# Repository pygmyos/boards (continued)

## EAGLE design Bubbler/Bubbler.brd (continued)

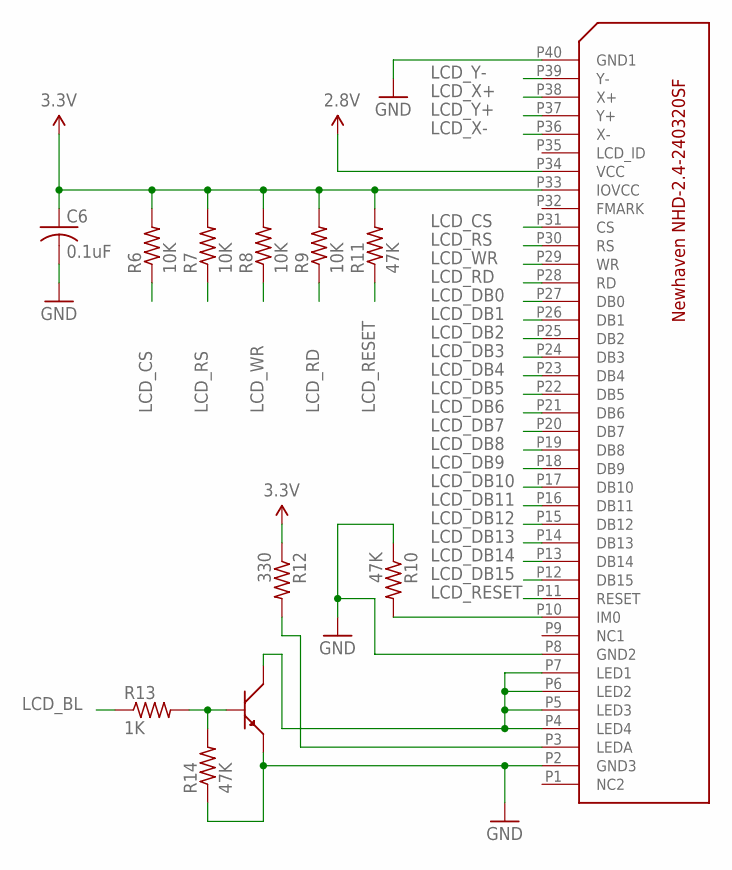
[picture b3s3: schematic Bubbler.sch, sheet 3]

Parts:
C6: 0.1uF; C0402
R6, R7, R8, R9: 10K; R0402
R10, R11, R14: 47K; R0402
R12: 330; R1206
R13: 1K; R0402
U4: BIPOLAR-PMBT6428; DUBLIB_SOT23
U$10: NHD-2.4-240320SF; MOLEX-534132-060

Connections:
2.8V: U$10.P34 (VCC); also elsewhere on the board
3.3V: C6.1, R6.2, R7.2, R8.2, R9.2, R11.2, R12.1, U$10.P33 (IOVCC); also elsewhere on the board
GND: C6.2, R10.1, R14.1, U4.2, U$10.P2 (GND3), U$10.P8 (GND2), U$10.P40 (GND1); also elsewhere on the board
LCD_BL: R13.1; also elsewhere on the board
LCD_CS: R6.1, U$10.P31 (CS); also elsewhere on the board
LCD_DB0: U$10.P27 (DB0); also elsewhere on the board
LCD_DB1: U$10.P26 (DB1); also elsewhere on the board
LCD_DB2: U$10.P25 (DB2); also elsewhere on the board
LCD_DB3: U$10.P24 (DB3); also elsewhere on the board
LCD_DB4: U$10.P23 (DB4); also elsewhere on the board
LCD_DB5: U$10.P22 (DB5); also elsewhere on the board
LCD_DB6: U$10.P21 (DB6); also elsewhere on the board
LCD_DB7: U$10.P20 (DB7); also elsewhere on the board
LCD_DB8: U$10.P19 (DB8); also elsewhere on the board
LCD_DB9: U$10.P18 (DB9); also elsewhere on the board
LCD_DB10: U$10.P17 (DB10); also elsewhere on the board
LCD_DB11: U$10.P16 (DB11); also elsewhere on the board
LCD_DB12: U$10.P15 (DB12); also elsewhere on the board
LCD_DB13: U$10.P14 (DB13); also elsewhere on the board
LCD_DB14: U$10.P13 (DB14); also elsewhere on the board
LCD_DB15: U$10.P12 (DB15); also elsewhere on the board
LCD_RD: R9.1, U$10.P28 (RD); also elsewhere on the board
LCD_RESET: R11.1, U$10.P11 (RESET); also elsewhere on the board
LCD_RS: R7.1, U$10.P30 (RS); also elsewhere on the board
LCD_WR: R8.1, U$10.P29 (WR); also elsewhere on the board
LCD_X+: U$10.P38 (X+); also elsewhere on the board
LCD_X-: U$10.P36 (X-); also elsewhere on the board
LCD_Y+: U$10.P37 (Y+); also elsewhere on the board
LCD_Y-: U$10.P39 (Y-); also elsewhere on the board
unnamed: R10.2, U$10.P10 (IM0)
unnamed: R12.2, U$10.P3 (LEDA)
unnamed: U4.3, U$10.P4 (LED4), U$10.P5 (LED3), U$10.P6 (LED2), U$10.P7 (LED1)
unnamed: R13.2, R14.2, U4.1

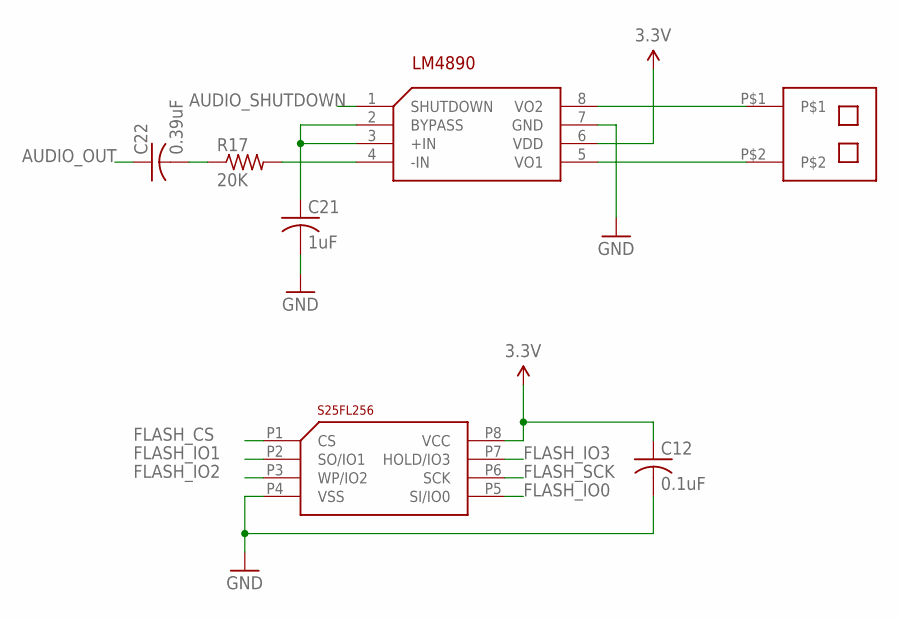
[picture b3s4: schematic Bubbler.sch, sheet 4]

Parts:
C12: 0.1uF; C0402
C21: 1uF; C0402
C22: 0.39uF; C0402
R17: 20K; R0402
U2: SPANSION-S25FL256; SPANSION-WSON-8
U3: LM4890; TSSOP8
U7: MOLEX-1.25-WTB-RA-CONN-2POS; MOLEX-1.25WTB-RA-CONN

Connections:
3.3V: C12.1, U2.P8 (VCC), U3.6 (VDD); also elsewhere on the board
AUDIO_OUT: C22.1; also elsewhere on the board
AUDIO_SHUTDOWN: U3.1 (SHUTDOWN)
FLASH_CS: U2.P1 (CS); also elsewhere on the board
FLASH_IO0: U2.P5 (SI/IO0); also elsewhere on the board
FLASH_IO1: U2.P2 (SO/IO1); also elsewhere on the board
FLASH_IO2: U2.P3 (WP/IO2); also elsewhere on the board
FLASH_IO3: U2.P7 (HOLD/IO3); also elsewhere on the board
FLASH_SCK: U2.P6 (SCK); also elsewhere on the board
GND: C12.2, C21.2, U2.P4 (VSS), U3.7 (GND), U7.P$3 (GND), U7.P$4 (GND); also elsewhere on the board
unnamed: U3.5 (VO1), U7.P$2
unnamed: U3.8 (VO2), U7.P$1
unnamed: C21.1, U3.2 (BYPASS), U3.3 (+IN)
unnamed: R17.2, U3.4 (-IN)
unnamed: C22.2, R17.1

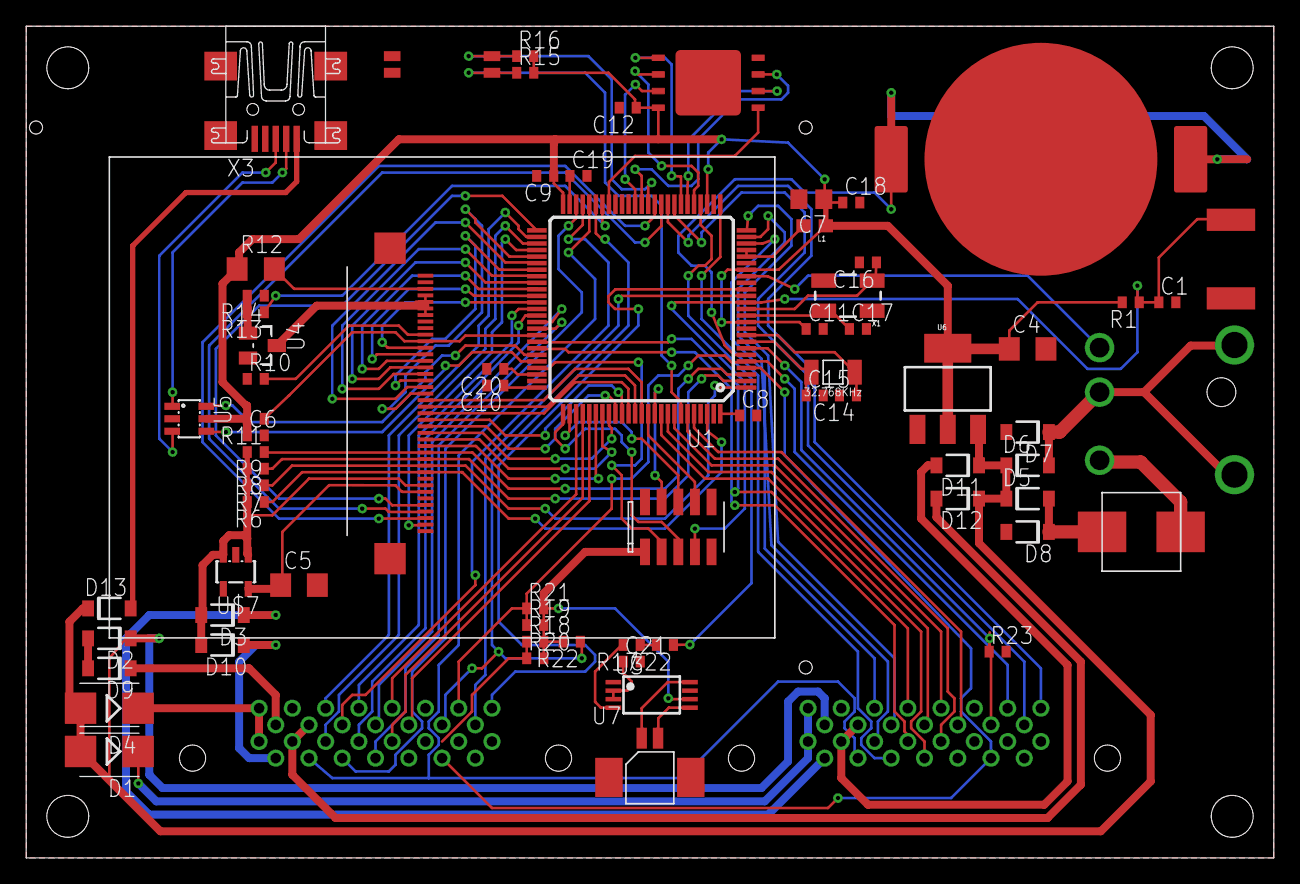
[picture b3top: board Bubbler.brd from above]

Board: 2 copper layers, 95.2 x 63.5 mm, 73 parts (0 on the bottom side), 113 nets.

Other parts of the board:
U$3: NHD-2.4-240320SF-OUTLINE

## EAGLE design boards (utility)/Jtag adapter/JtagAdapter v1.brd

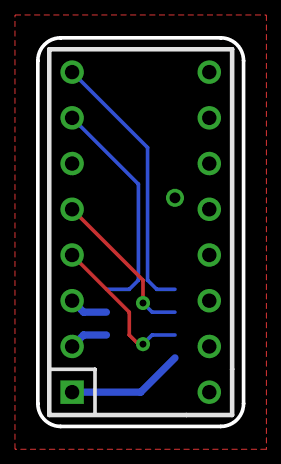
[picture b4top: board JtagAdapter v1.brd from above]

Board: 2 copper layers, 11.4 x 21.6 mm, 3 parts (1 on the bottom side), 8 nets.

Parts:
INFO3: Evan Teitelman; %CC-NC-SA
U$1: STM32-JTAG-10PSTM32-JTAG-ADAPTER(INVERTED); STM32-JTAG-10P
U$2: IDC-DIP-2P16-EIDC-DIP-2P16-E; IDC-DIP-2P16-E

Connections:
3.3V: U$1.2, U$2.P1
GND: U$1.1, U$1.10, U$2.P4, U$2.P6, U$2.P8, U$2.P10, U$2.P12, U$2.P14, U$2.P16
JTCK: U$1.6, U$2.P9
JTDI: U$1.5, U$2.P5
JTDO: U$1.7, U$2.P13
JTMS: U$1.4, U$2.P7
JTRST: U$1.3, U$2.P3
RST: U$1.8, U$2.P15

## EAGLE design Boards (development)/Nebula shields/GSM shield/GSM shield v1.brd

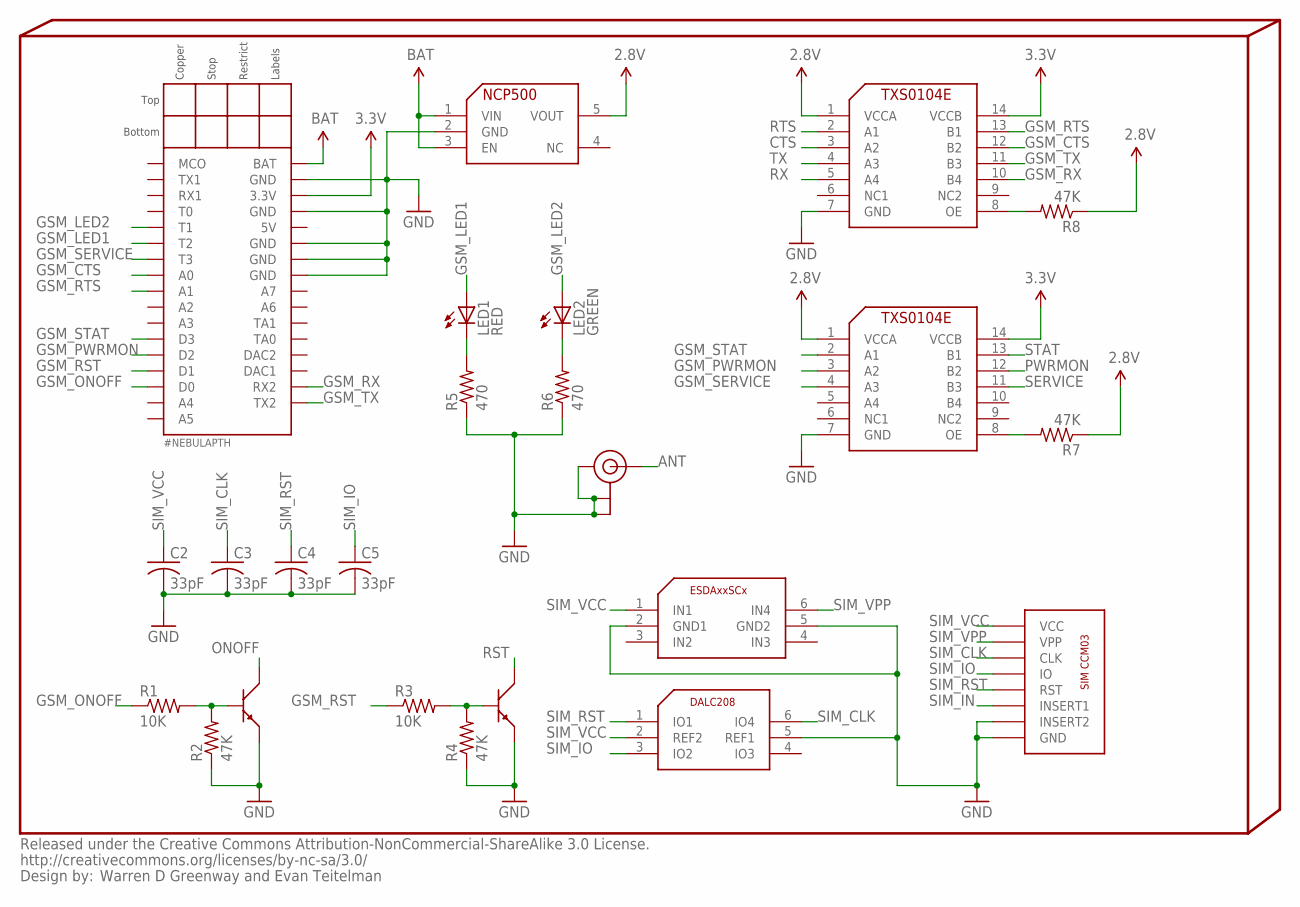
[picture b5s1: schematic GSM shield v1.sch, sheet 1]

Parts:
C2, C3, C4, C5: 33pF; C0402
INFO3: Warren D Greenway and Evan Teitelman; %CC-NC-SA
LED1: RED; LED-0603
LED2: GREEN; LED-0603
NEBULA1: #NEBULAPTH; #NEBULA-PTH
R1, R3: 10K; R0402
R2, R4, R7, R8: 47K; R0402
R5, R6: 470; R0402
U2, U6: BIPOLAR-PMBT6428; DUBLIB_SOT23
U3: NCP500; SOT23-5L
U4: ESDAXXSC6; SOT23-6L
U5: CCM03-3009; CCM03-300X
U7: DALC208; SOT23-6L
U8, U9: INTERFACE-TXS0104E; PW_R-PDSO-G14
U$1: U.FL

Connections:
2.8V: R7.1, R8.1, U3.5 (VOUT), U8.1 (VCCA), U9.1 (VCCA)
3.3V: NEBULA1.3.3V, U8.14 (VCCB), U9.14 (VCCB)
ANT: U$1.P$3 (SIGNAL); also elsewhere on the board
BAT: NEBULA1.BAT, U3.1 (VIN), U3.3 (EN); also elsewhere on the board
CTS: U9.3 (A2); also elsewhere on the board
GND: C2.2, C3.2, C4.2, C5.2, NEBULA1.GND1 (GND), NEBULA1.GND2 (GND), NEBULA1.GND3 (GND), NEBULA1.GND4 (GND), NEBULA1.GND5 (GND), R2.1, R4.1, R5.1, R6.1, U2.2, U3.2 (GND), U4.2 (GND1), U4.5 (GND2), U5.C5 (GND), U5.P2 (INSERT2), U6.2, U7.5 (REF1), U8.7 (GND), U9.7 (GND), U$1.P$1 (GND), U$1.P$2 (GND), U$1.P$4 (SHELL); also elsewhere on the board
GSM_CTS: NEBULA1.A0, U9.12 (B2)
GSM_LED1: LED1.A, NEBULA1.T2
GSM_LED2: LED2.A, NEBULA1.T1
GSM_ONOFF: NEBULA1.D0, R1.1
GSM_PWRMON: NEBULA1.D2, U8.3 (A2)
GSM_RST: NEBULA1.D1, R3.1
GSM_RTS: NEBULA1.A1, U9.13 (B1)
GSM_RX: NEBULA1.COM2_RX (RX2), U9.10 (B4)
GSM_SERVICE: NEBULA1.T3, U8.4 (A3)
GSM_STAT: NEBULA1.D3, U8.2 (A1)
GSM_TX: NEBULA1.COM2_TX (TX2), U9.11 (B3)
unnamed: R7.2, U8.8 (OE)
unnamed: R8.2, U9.8 (OE)
unnamed: R1.2, R2.2, U2.1
unnamed: R3.2, R4.2, U6.1
unnamed: LED1.C, R5.2
unnamed: LED2.C, R6.2
ONOFF: U2.3; also elsewhere on the board
PWRMON: U8.12 (B2); also elsewhere on the board
RST: U6.3; also elsewhere on the board
RTS: U9.2 (A1); also elsewhere on the board
RX: U9.5 (A4); also elsewhere on the board
SERVICE: U8.11 (B3); also elsewhere on the board
SIM_CLK: C3.1, U5.C3 (CLK), U7.6 (IO4); also elsewhere on the board
SIM_IN: U5.P1 (INSERT1); also elsewhere on the board
SIM_IO: C5.1, U5.C7 (IO), U7.3 (IO2); also elsewhere on the board
SIM_RST: C4.1, U5.C2 (RST), U7.1 (IO1); also elsewhere on the board
SIM_VCC: C2.1, U4.1 (IN1), U5.C1 (VCC), U7.2 (REF2); also elsewhere on the board
SIM_VPP: U4.6 (IN4), U5.C6 (VPP)
STAT: U8.13 (B1); also elsewhere on the board
TX: U9.4 (A3); also elsewhere on the board

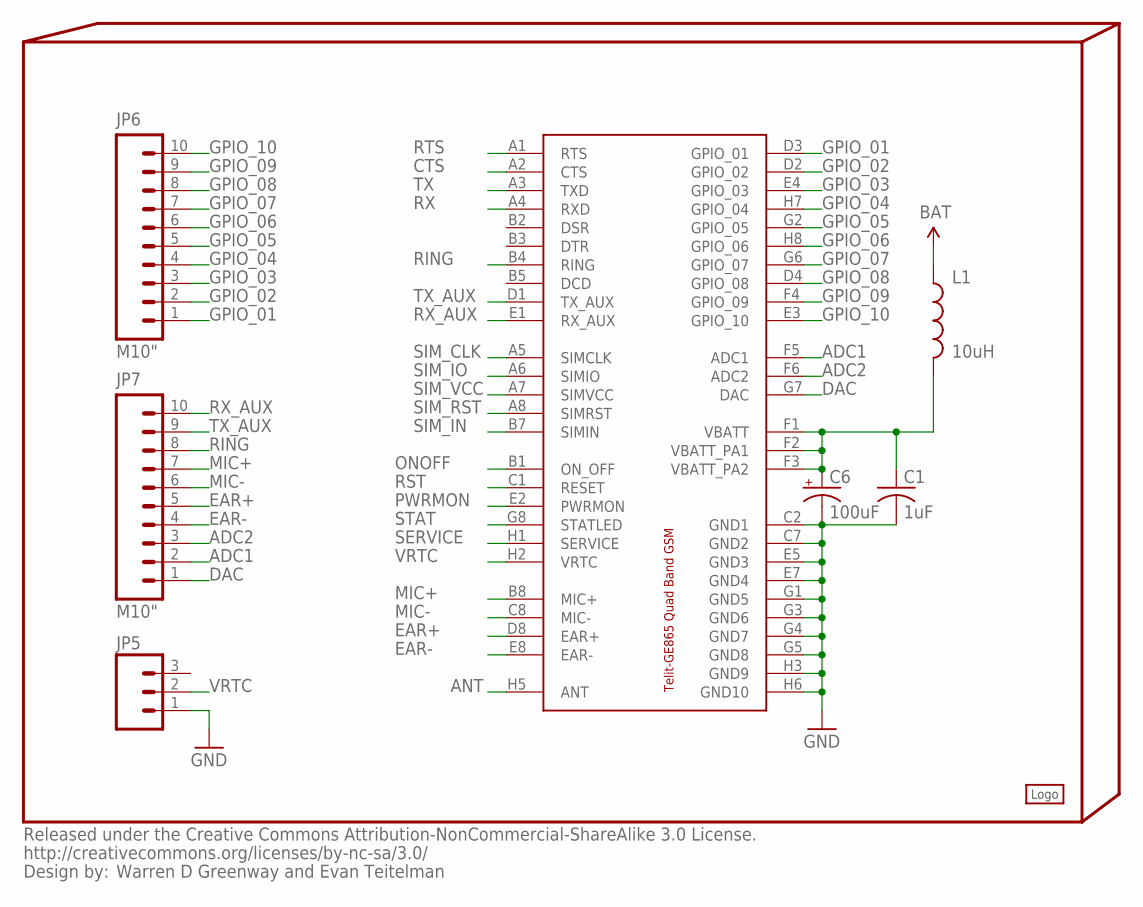
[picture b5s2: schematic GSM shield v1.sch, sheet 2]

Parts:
C1: 1uF; C0402
C6: 100uF; EIA6032
JP5: M03PTH; 1X03
JP6, JP7: M10"; 1X10
L1: 10uH; 1210
LOGO2: #PYGMYLOGOLARGE; #PYGMYLOGO
U11: TELIT-GE865T; TELIT-GE865

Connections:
ADC1: JP7.2, U11.F5 (ADC1)
ADC2: JP7.3, U11.F6 (ADC2)
ANT: U11.H5 (ANT); also elsewhere on the board
BAT: L1.1; also elsewhere on the board
CTS: U11.A2 (CTS); also elsewhere on the board
DAC: JP7.1, U11.G7 (DAC)
EAR+: JP7.5, U11.D8 (EAR+)
EAR-: JP7.4, U11.E8 (EAR-)
GND: C1.2, C6.P$2 (-), JP5.1, U11.C2 (GND1), U11.C7 (GND2), U11.E5 (GND3), U11.E7 (GND4), U11.G1 (GND5), U11.G3 (GND6), U11.G4 (GND7), U11.G5 (GND8), U11.H3 (GND9), U11.H6 (GND10); also elsewhere on the board
GPIO_01: JP6.1, U11.D3 (GPIO_01)
GPIO_02: JP6.2, U11.D2 (GPIO_02)
GPIO_03: JP6.3, U11.E4 (GPIO_03)
GPIO_04: JP6.4, U11.H7 (GPIO_04)
GPIO_05: JP6.5, U11.G2 (GPIO_05)
GPIO_06: JP6.6, U11.H8 (GPIO_06)
GPIO_07: JP6.7, U11.G6 (GPIO_07)
GPIO_08: JP6.8, U11.D4 (GPIO_08)
GPIO_09: JP6.9, U11.F4 (GPIO_09)
GPIO_10: JP6.10, U11.E3 (GPIO_10)
MIC+: JP7.7, U11.B8 (MIC+)
MIC-: JP7.6, U11.C8 (MIC-)
unnamed: C1.1, C6.P$1 (+), L1.2, U11.F1 (VBATT), U11.F2 (VBATT_PA1), U11.F3 (VBATT_PA2)
ONOFF: U11.B1 (ON_OFF); also elsewhere on the board
PWRMON: U11.E2 (PWRMON); also elsewhere on the board
RING: JP7.8, U11.B4 (RING)
RST: U11.C1 (RESET); also elsewhere on the board
RTS: U11.A1 (RTS); also elsewhere on the board
RX: U11.A4 (RXD); also elsewhere on the board
RX_AUX: JP7.10, U11.E1 (RX_AUX)
SERVICE: U11.H1 (SERVICE); also elsewhere on the board
SIM_CLK: U11.A5 (SIMCLK); also elsewhere on the board
SIM_IN: U11.B7 (SIMIN); also elsewhere on the board
SIM_IO: U11.A6 (SIMIO); also elsewhere on the board
SIM_RST: U11.A8 (SIMRST); also elsewhere on the board
SIM_VCC: U11.A7 (SIMVCC); also elsewhere on the board
STAT: U11.G8 (STATLED); also elsewhere on the board
TX: U11.A3 (TXD); also elsewhere on the board
TX_AUX: JP7.9, U11.D1 (TX_AUX)
VRTC: JP5.2, U11.H2 (VRTC)

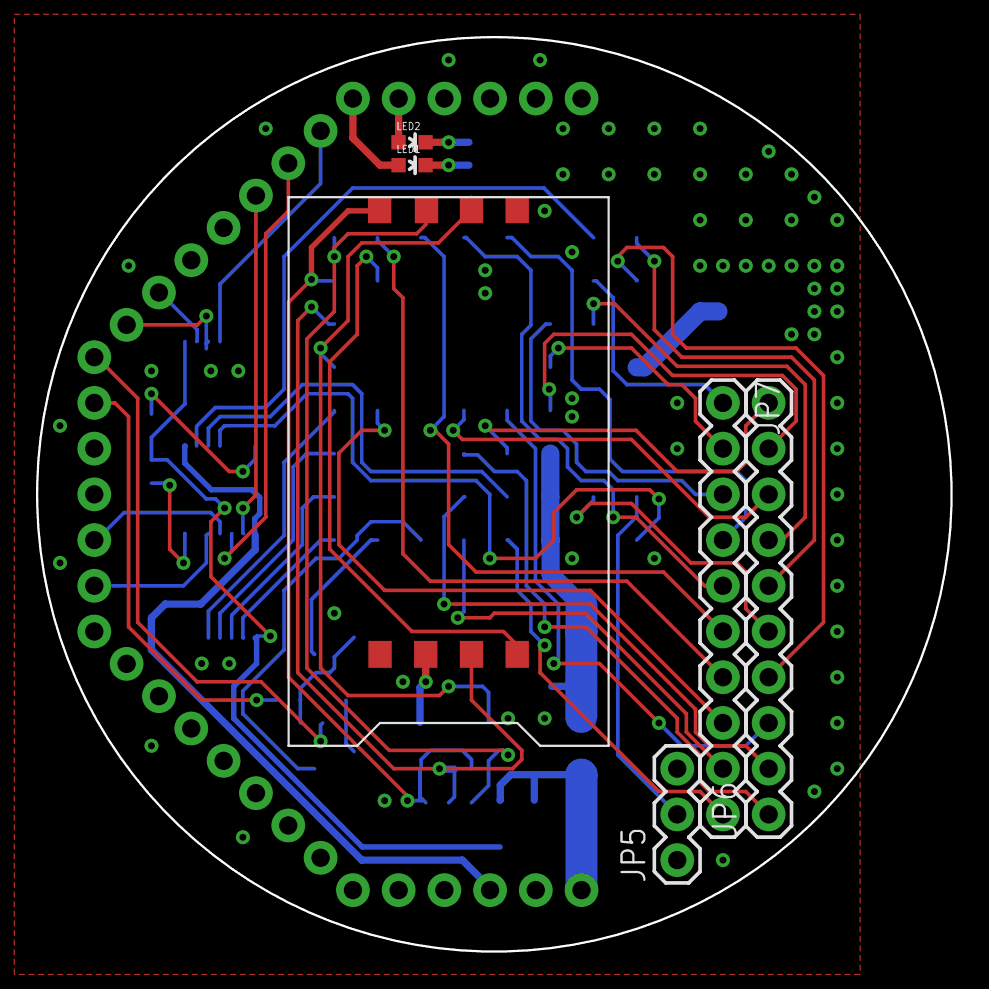
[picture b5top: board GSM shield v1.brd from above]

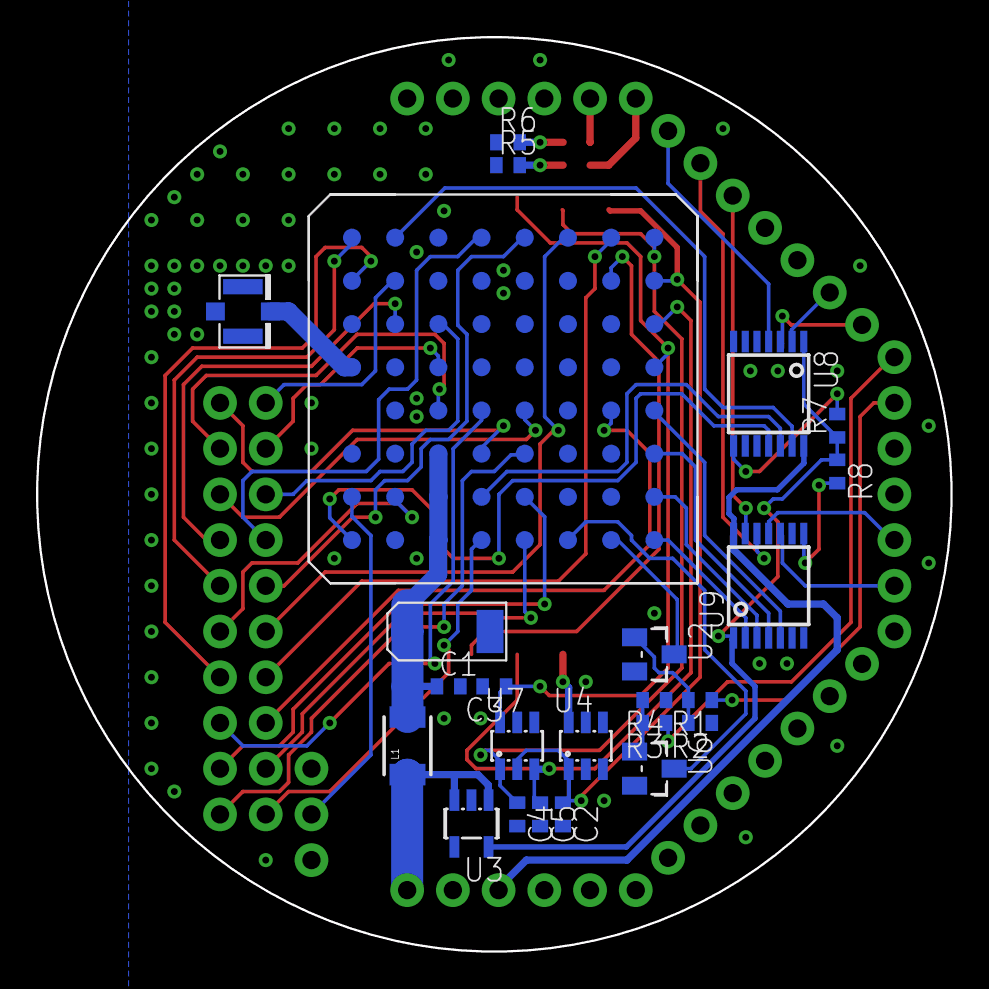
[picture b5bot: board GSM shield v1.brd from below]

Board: 2 copper layers, 50.8 x 50.8 mm, 33 parts (24 on the bottom side), 59 nets.

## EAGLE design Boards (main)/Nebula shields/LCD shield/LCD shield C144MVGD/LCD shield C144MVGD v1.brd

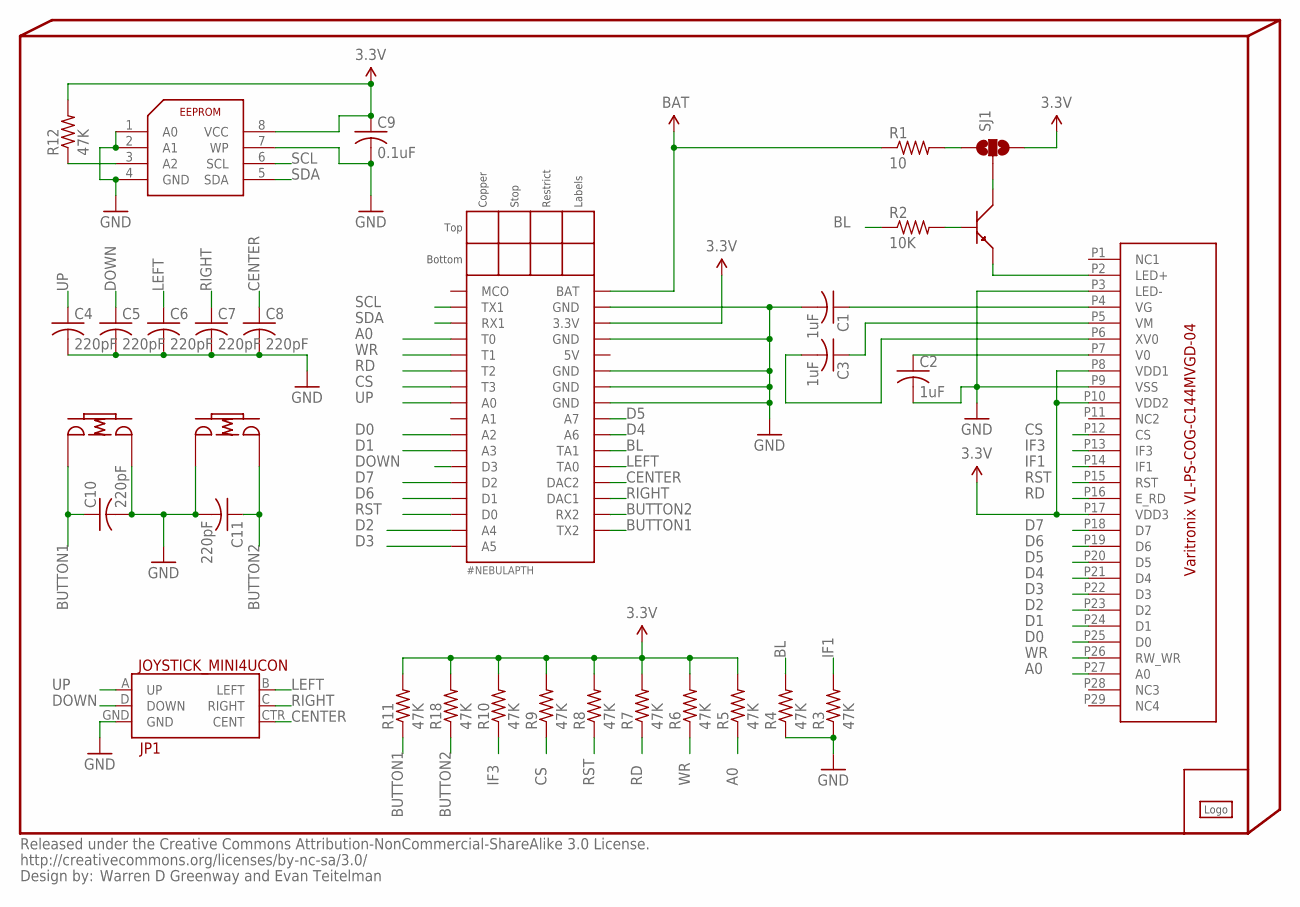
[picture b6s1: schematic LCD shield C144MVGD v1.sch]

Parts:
C1, C2, C3: 1uF; C0402
C4, C5, C6, C7, C8, C10, C11: 220pF; C0402
C9: 0.1uF; C0402
INFO3: Warren D Greenway and Evan Teitelman; %CC-NC-SA
JP1: JOYSTICK_MINI4UCON; JOYSTICK_MINI
LOGO1: #PYGMYLOGOLARGE; #PYGMYLOGO
NEBULA1: #NEBULAPTH; #NEBULA-PTH
R1: 10; R0805
R2: 10K; R0402
R3, R4, R5, R6, R7, R8, R9, R10, R11, R12, R18: 47K; R0402
SJ1: SOLDERJUMPER_2WAYPASTE1&2; SJ_3_PASTE1&2
U1: VARITRONIX_VL-PS-COG-C144MVGD-04FOLDED; VARITRONIX_C144MVGD_FOLDED
U2: BIPOLAR-PMBT6428; DUBLIB_SOT23
U3: EEPROM-ATMEL-AT24HC02B; TSSOP8
U4, U5: SWITCH-ALPS-SKRG; SWITCH-2P-5MM

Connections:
3.3V: C9.1, NEBULA1.3.3V, R5.2, R6.2, R7.2, R8.2, R9.2, R10.2, R11.2, R12.2, R18.2, SJ1.3, U1.P8 (VDD1), U1.P10 (VDD2), U1.P17 (VDD3), U3.8 (VCC)
A0: NEBULA1.T0, R5.1, U1.P27 (A0)
BAT: NEBULA1.BAT, R1.1
BL: NEBULA1.TA1, R2.1, R4.2
BUTTON1: C10.1, NEBULA1.COM2_TX (TX2), R11.1, U4.P1
BUTTON2: C11.1, NEBULA1.COM2_RX (RX2), R18.1, U5.P2
CENTER: C8.1, JP1.CTR (CENT), NEBULA1.DAC2
CS: NEBULA1.T3, R9.1, U1.P12 (CS)
D0: NEBULA1.A2, U1.P25 (D0)
D1: NEBULA1.A3, U1.P24 (D1)
D2: NEBULA1.A4, U1.P23 (D2)
D3: NEBULA1.A5, U1.P22 (D3)
D4: NEBULA1.A6, U1.P21 (D4)
D5: NEBULA1.A7, U1.P20 (D5)
D6: NEBULA1.D1, U1.P19 (D6)
D7: NEBULA1.D2, U1.P18 (D7)
DOWN: C5.1, JP1.D (DOWN), NEBULA1.D3
GND: C1.2, C2.2, C4.2, C5.2, C6.2, C7.2, C8.2, C9.2, C10.2, C11.2, JP1.GND, NEBULA1.GND1 (GND), NEBULA1.GND2 (GND), NEBULA1.GND3 (GND), NEBULA1.GND4 (GND), NEBULA1.GND5 (GND), R3.1, R4.1, U1.P3 (LED-), U1.P9 (VSS), U3.1 (A0), U3.2 (A1), U3.4 (GND), U3.7 (WP), U4.P2, U5.P1
IF1: R3.2, U1.P14 (IF1)
IF3: R10.1, U1.P13 (IF3)
LEFT: C6.1, JP1.B (LEFT), NEBULA1.TA0
unnamed: C1.1, U1.P4 (VG)
unnamed: C3.1, U1.P5 (VM)
unnamed: C3.2, U1.P6 (XV0)
unnamed: C2.1, U1.P7 (V0)
unnamed: SJ1.2, U2.3
unnamed: U1.P2 (LED+), U2.2
unnamed: R2.2, U2.1
unnamed: R1.2, SJ1.1
unnamed: R12.1, U3.3 (A2)
RD: NEBULA1.T2, R7.1, U1.P16 (E_RD)
RIGHT: C7.1, JP1.C (RIGHT), NEBULA1.DAC1
RST: NEBULA1.D0, R8.1, U1.P15 (RST)
SCL: NEBULA1.COM1_TX (TX1), U3.6 (SCL)
SDA: NEBULA1.COM1_RX (RX1), U3.5 (SDA)
UP: C4.1, JP1.A (UP), NEBULA1.A0
WR: NEBULA1.T1, R6.1, U1.P26 (RW_WR)

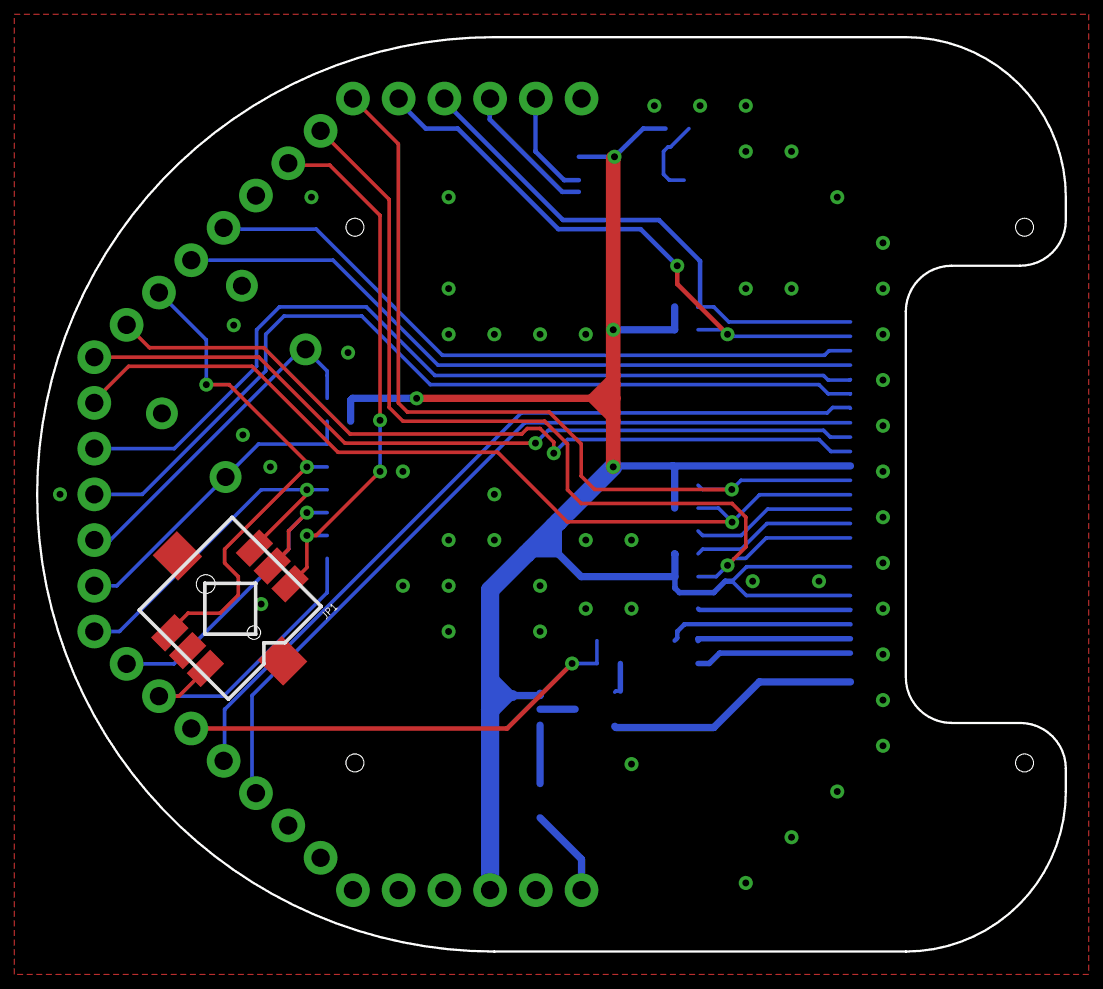
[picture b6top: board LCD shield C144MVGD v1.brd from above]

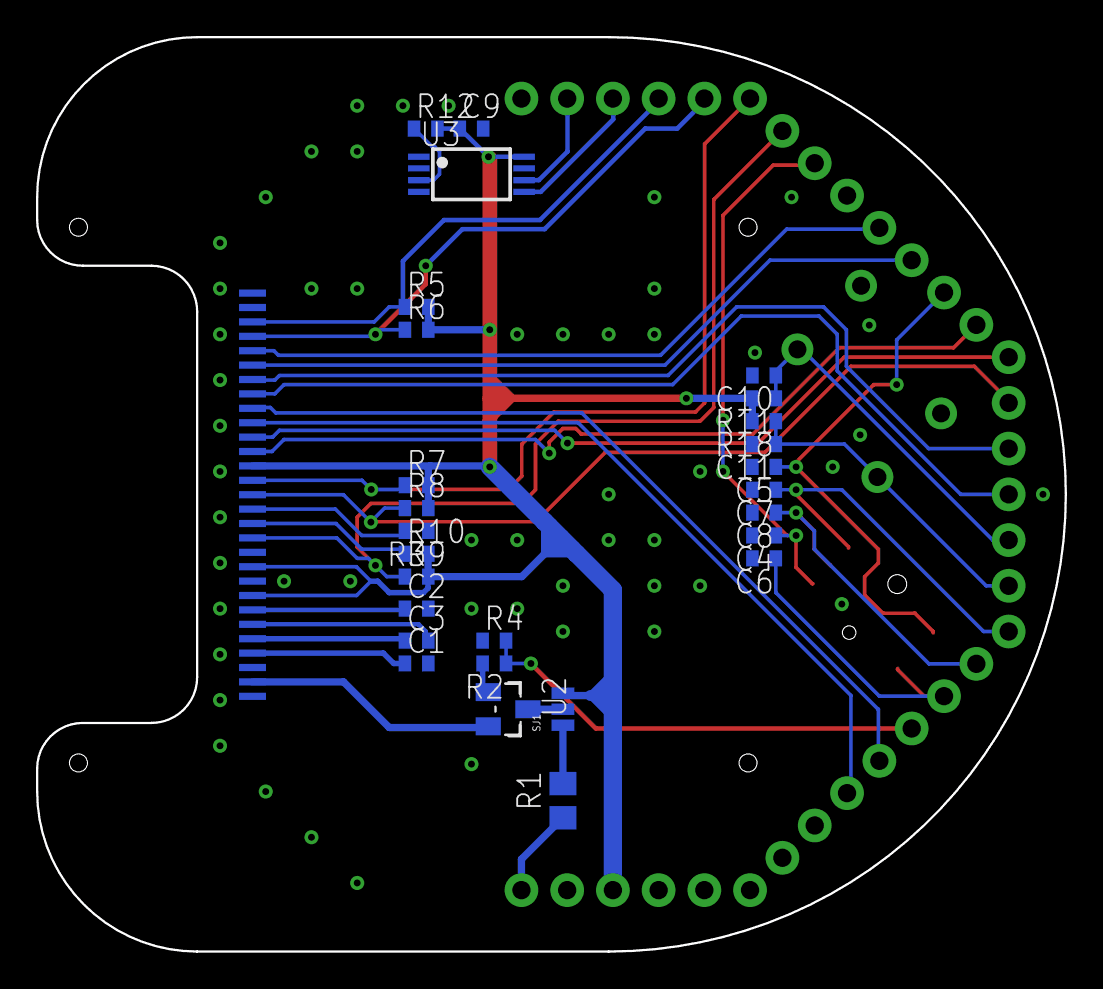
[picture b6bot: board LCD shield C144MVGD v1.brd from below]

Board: 2 copper layers, 57.1 x 50.8 mm, 34 parts (28 on the bottom side), 37 nets.

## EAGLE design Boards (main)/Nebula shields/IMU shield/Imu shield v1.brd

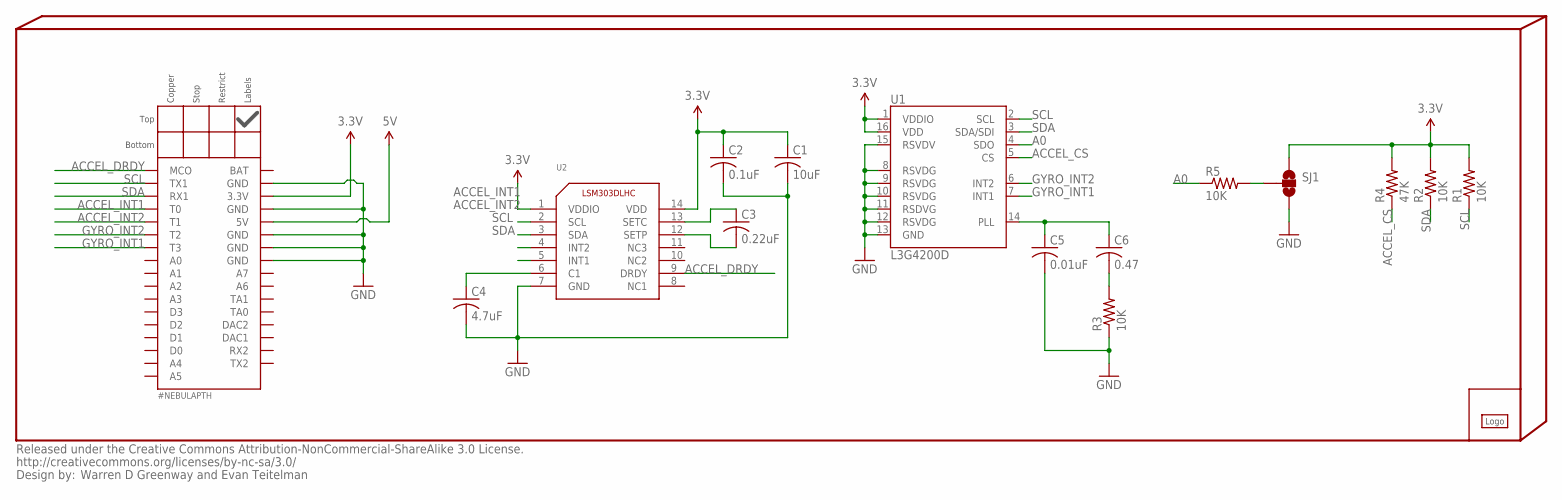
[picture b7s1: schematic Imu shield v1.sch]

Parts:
C1: 10uF; C0805
C2: 0.1uF; C0402
C3: 0.22uF; C0402
C4: 4.7uF; C0402
C5: 0.01uF; C0402
C6: 0.47; C0402
INFO2: Warren D Greenway and Evan Teitelman; %CC-NC-SA
LOGO1: #PYGMYLOGONORMAL; #PYGMYLOGO
NEBULA1: #NEBULAPTH; #NEBULA-PTH
NEBULAPART1: #NEBULA-PARTLABELS-TOP; #NEBULA-LABELS-TOP
R1, R2, R3, R5: 10K; R0402
R4: 47K; R0402
SJ1: SOLDERJUMPER_2WAYPASTE1&2; SJ_3_PASTE1&2
U1: L3G4200D; LGA16-4X4
U2: FREESCALE-LSM303DLHC; LGA14

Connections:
3.3V: C1.1, C2.1, NEBULA1.3.3V, R1.2, R2.2, R4.2, SJ1.1, U1.1 (VDDIO), U1.16 (VDD), U2.1 (VDDIO), U2.14 (VDD)
5V: NEBULA1.5V
A0: R5.1, U1.4 (SDO)
ACCEL_CS: R4.1, U1.5 (CS)
ACCEL_DRDY: NEBULA1.MCO, U2.9 (DRDY)
ACCEL_INT1: NEBULA1.T0, U2.4 (INT2)
ACCEL_INT2: NEBULA1.T1, U2.5 (INT1)
GND: C1.2, C2.2, C4.2, C5.2, NEBULA1.GND1 (GND), NEBULA1.GND2 (GND), NEBULA1.GND3 (GND), NEBULA1.GND4 (GND), NEBULA1.GND5 (GND), R3.1, SJ1.3, U1.8 (RSVDG), U1.9 (RSVDG), U1.10 (RSVDG), U1.11 (RSDVG), U1.12 (RSVDG), U1.13 (GND), U1.15 (RSVDV), U2.7 (GND)
GYRO_INT1: NEBULA1.T3, U1.7 (INT1)
GYRO_INT2: NEBULA1.T2, U1.6 (INT2)
unnamed: C4.1, U2.6 (C1)
unnamed: C5.1, C6.1, U1.14 (PLL)
unnamed: C3.1, U2.13 (SETC)
unnamed: C3.2, U2.12 (SETP)
unnamed: R5.2, SJ1.2
unnamed: C6.2, R3.2
SCL: NEBULA1.COM1_TX (TX1), R1.1, U1.2 (SCL), U2.2 (SCL)
SDA: NEBULA1.COM1_RX (RX1), R2.1, U1.3 (SDA/SDI), U2.3 (SDA)

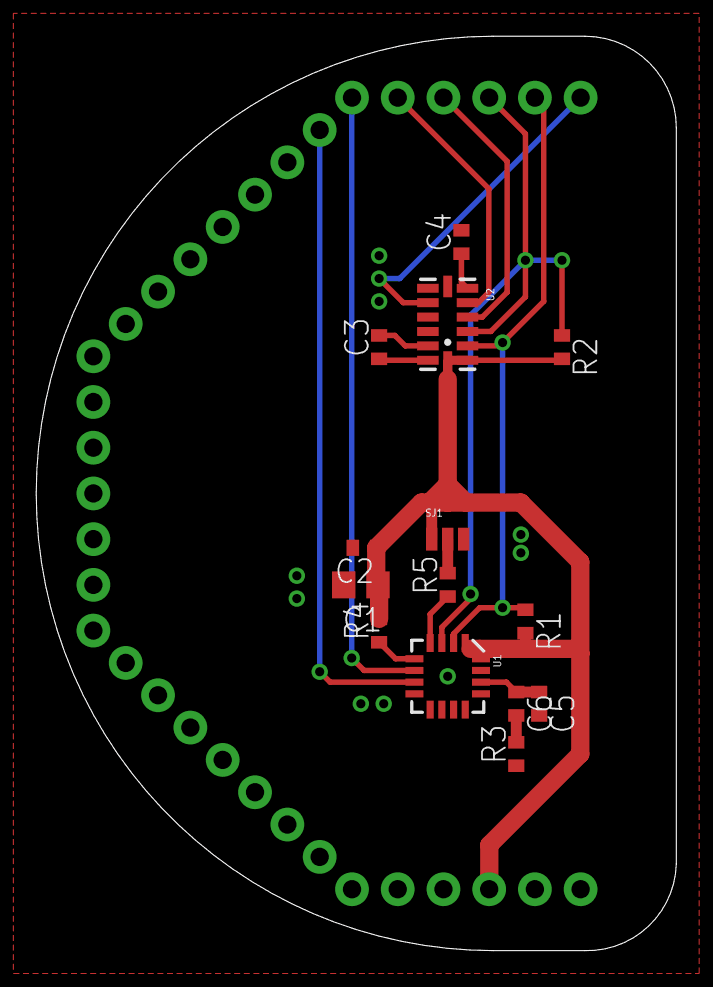
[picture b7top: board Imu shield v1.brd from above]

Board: 2 copper layers, 35.6 x 50.8 mm, 18 parts (1 on the bottom side), 17 nets.

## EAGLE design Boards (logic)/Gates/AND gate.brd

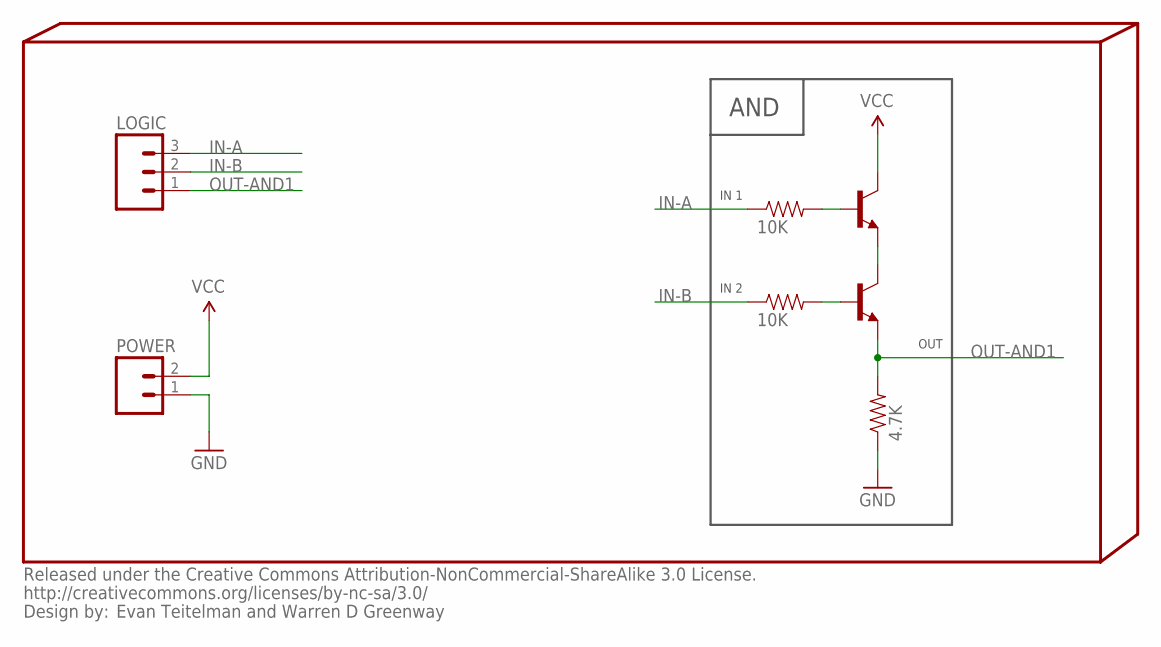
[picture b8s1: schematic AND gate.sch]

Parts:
INFO4: Evan Teitelman and Warren D Greenway; %CC-NC-SA
LOGIC: M03PTH; 1X03
PDR-AND1: 4.7K; 0402-RES
POWER: M02PTH; 1X02
Q1-AND1, Q2-AND1: TRANSISTOR_NPNSOT23; SOT23
R1-AND1, R2-AND1: 10K; 0402-RES

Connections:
GND: PDR-AND1.1, POWER.1
IN-A: LOGIC.3, R1-AND1.1
IN-B: LOGIC.2, R2-AND1.1
unnamed: Q1-AND1.1 (B), R1-AND1.2
unnamed: Q2-AND1.1 (B), R2-AND1.2
OUT-AND1: LOGIC.1, PDR-AND1.2, Q2-AND1.2 (E)
Q-Q-AND1: Q1-AND1.2 (E), Q2-AND1.3 (C)
VCC: POWER.2, Q1-AND1.3 (C)

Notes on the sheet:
AND
IN 2
OUT
IN 1

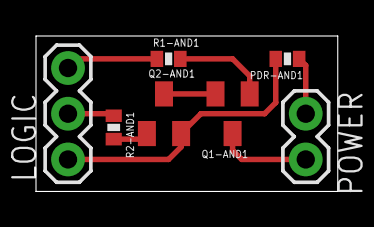
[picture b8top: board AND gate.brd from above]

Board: 2 copper layers, 16.8 x 8.6 mm, 8 parts (0 on the bottom side), 8 nets.
